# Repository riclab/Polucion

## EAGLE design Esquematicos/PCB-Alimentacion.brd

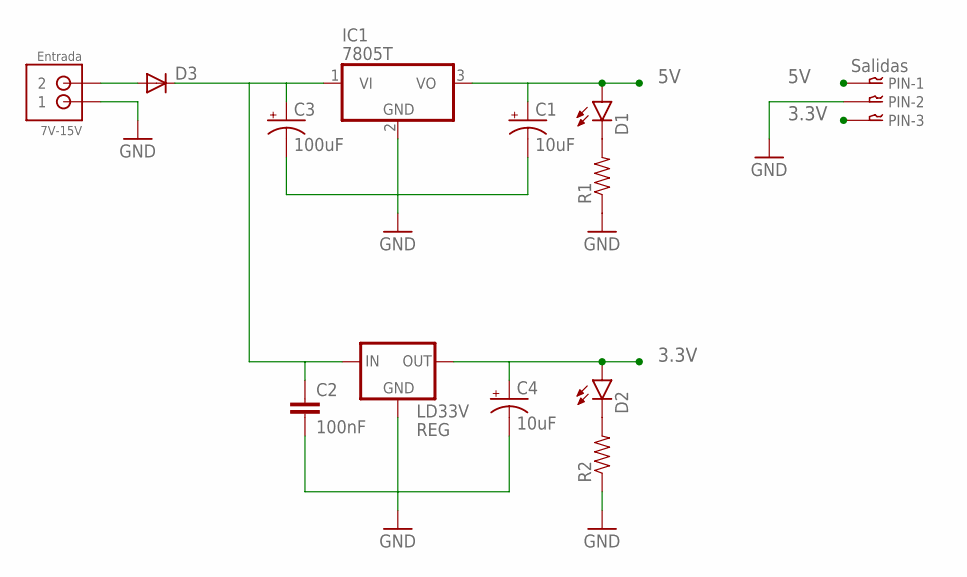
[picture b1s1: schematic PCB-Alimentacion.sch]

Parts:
7V-15V: Entrada; JST_B2B-PH_HEADER
C1, C4: 10uF; CPOL-RADIAL-10UF-25V
C2: 100nF; AXIAL-5MM
C3: 100uF; CPOL-RADIAL-10UF-25V
D1, D2: LED3MM
D3: DIODE-DO-214AC; DO-214AC
IC1: 7805T; TO220H
LD33V: REG; 78XXL
PIN: Salidas; B3B-XH
R1, R2: RESISTORKIT; AXIAL-0.3-KIT

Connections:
3.3V: C4.1 (+), D2.A, LD33V.GND (OUT), PIN.P$3
5V: C1.1 (+), D1.A, IC1.3 (VO), PIN.P$1
GND: 7V-15V.P1 (1), C1.2 (-), C2.P$2 (2), C3.2 (-), C4.2 (-), IC1.2 (GND), LD33V.IN (GND), PIN.P$2, R1.P$1 (1), R2.P$1 (1)
unnamed: C2.P$1 (1), C3.1 (+), D3.C, IC1.1 (VI), LD33V.OUT (IN)
unnamed: D1.K (C), R1.P$2 (2)
unnamed: 7V-15V.P2 (2), D3.A
unnamed: D2.K (C), R2.P$2 (2)

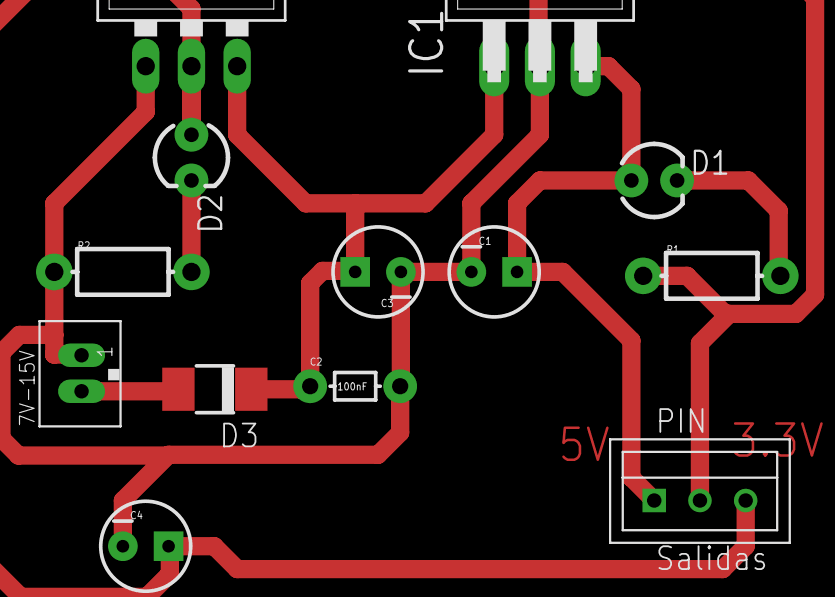
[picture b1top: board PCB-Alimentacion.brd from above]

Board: 2 copper layers, 13 parts (0 on the bottom side), 7 nets.

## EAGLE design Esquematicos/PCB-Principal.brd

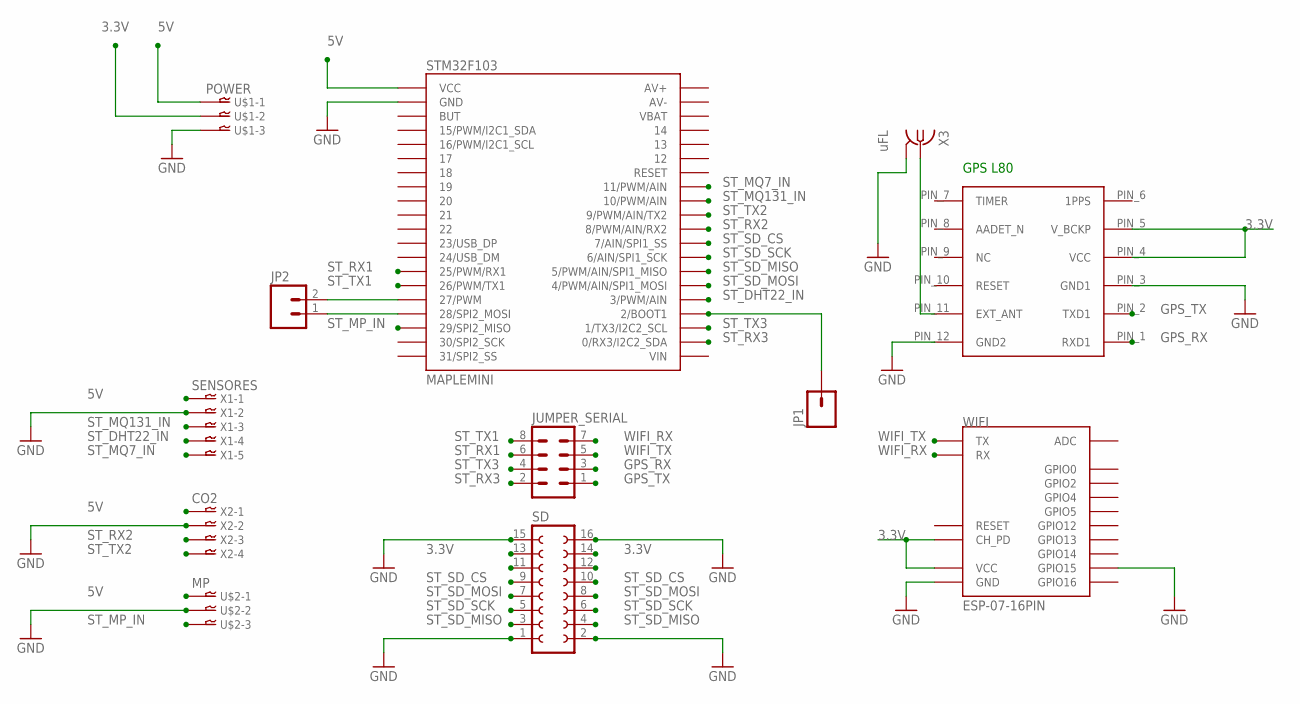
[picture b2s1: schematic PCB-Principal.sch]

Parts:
GPS1: GPSL80; L80
JP1: M01PTH_LONGPAD; 1X01_LONGPAD
JP2: M02PTH3; 1X02_LONGPADS
JUMPER_SERIAL: MA04-2
SD: FE08-2
STM32F103: MAPLEMINI; 20-DIP
U$1: POWER; B3B-XH
U$2: MP; B3B-XH
WIFI: ESP-07-16PIN
X1: SENSORES; B5B-XH
X2: CO2; B4B-XH
X3: uFL; IPEX-20279-001E

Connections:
3.3V: GPS1.PIN_4 (VCC), GPS1.PIN_5 (V_BCKP), SD.13, SD.14, U$1.P$2, WIFI.CH_PD, WIFI.VCC
5V: STM32F103.1 (VCC), U$1.P$1, U$2.P$1, X1.P$1, X2.P$1
GND: GPS1.PIN_3 (GND1), GPS1.PIN_12 (GND2), SD.1, SD.2, SD.15, SD.16, STM32F103.2 (GND), U$1.P$3, U$2.P$2, WIFI.GND, WIFI.GPIO15, X1.P$2, X2.P$2, X3.2@1 (GND), X3.2@2 (GND)
GPS_RX: GPS1.PIN_1 (RXD1), JUMPER_SERIAL.3
GPS_TX: GPS1.PIN_2 (TXD1), JUMPER_SERIAL.1
unnamed: JP1.1, STM32F103.24 (2/BOOT1)
unnamed: GPS1.PIN_11 (EXT_ANT), X3.1
unnamed: JP2.2, STM32F103.16 (27/PWM)
unnamed: JP2.1, STM32F103.17 (28/SPI2_MOSI)
ST_DHT22_IN: STM32F103.25 (3/PWM/AIN), X1.P$4
ST_MP_IN: STM32F103.18 (29/SPI2_MISO), U$2.P$3
ST_MQ7_IN: STM32F103.33 (11/PWM/AIN), X1.P$5
ST_MQ131_IN: STM32F103.32 (10/PWM/AIN), X1.P$3
ST_RX1: JUMPER_SERIAL.6, STM32F103.14 (25/PWM/RX1)
ST_RX2: STM32F103.30 (8/PWM/AIN/RX2), X2.P$3
ST_RX3: JUMPER_SERIAL.2, STM32F103.22 (0/RX3/I2C2_SDA)
ST_SD_CS: SD.9, SD.10, STM32F103.29 (7/AIN/SPI1_SS)
ST_SD_MISO: SD.3, SD.4, STM32F103.27 (5/PWM/AIN/SPI1_MISO)
ST_SD_MOSI: SD.7, SD.8, STM32F103.26 (4/PWM/AIN/SPI1_MOSI)
ST_SD_SCK: SD.5, SD.6, STM32F103.28 (6/AIN/SPI1_SCK)
ST_TX1: JUMPER_SERIAL.8, STM32F103.15 (26/PWM/TX1)
ST_TX2: STM32F103.31 (9/PWM/AIN/TX2), X2.P$4
ST_TX3: JUMPER_SERIAL.4, STM32F103.23 (1/TX3/I2C2_SCL)
WIFI_RX: JUMPER_SERIAL.7, WIFI.RX
WIFI_TX: JUMPER_SERIAL.5, WIFI.TX

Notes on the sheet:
GPS L80

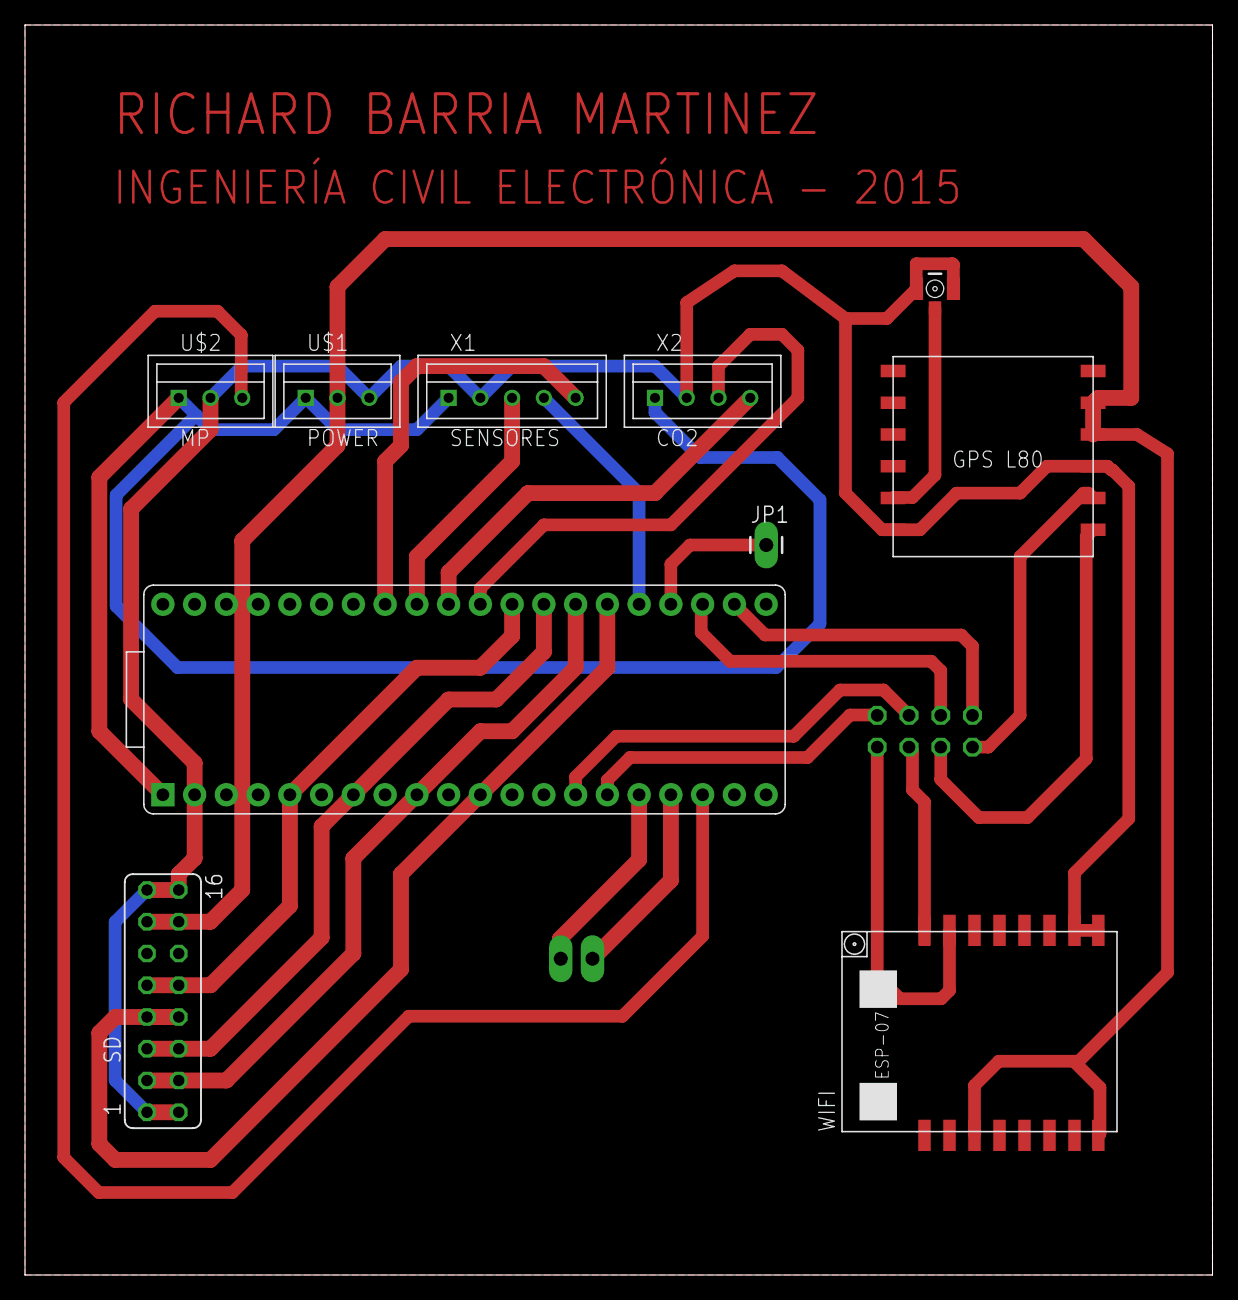
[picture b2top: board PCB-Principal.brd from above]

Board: 2 copper layers, 95.0 x 100.0 mm, 12 parts (1 on the bottom side), 25 nets.

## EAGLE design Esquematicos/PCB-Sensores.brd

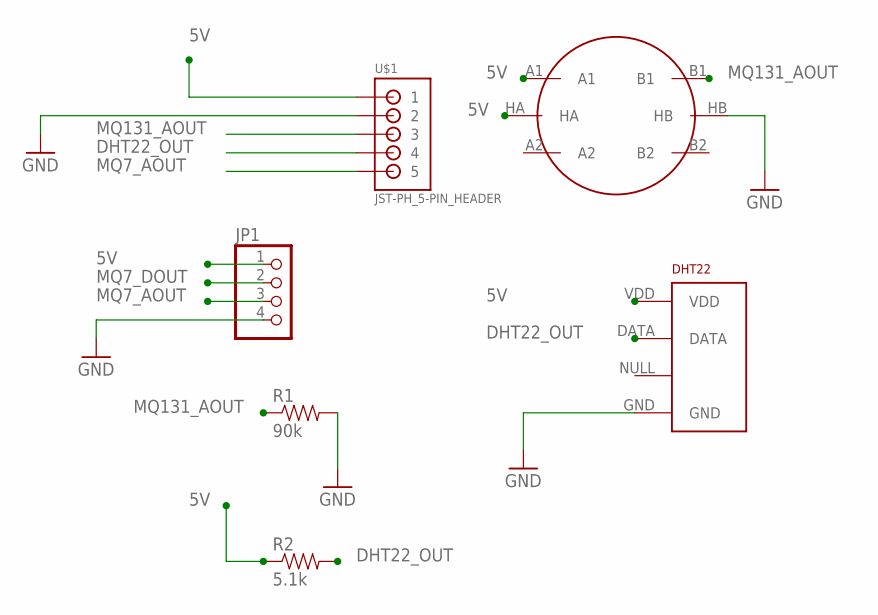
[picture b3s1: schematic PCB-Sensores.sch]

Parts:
DHT22: RHT03_DHT-22_AM2302; RHT03_DHT-22
JP1: PINHD-1X4; 1X04
MQ131: METHANE_SENSOR; MQ-3
R1: 90k; AXIAL-0.3EZ
R2: 5.1k; AXIAL-0.3EZ
U$1: JST-PH_5-PIN_HEADER; JST_B5B-PH_HEADER

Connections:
5V: DHT22.VDD, JP1.1, MQ131.A1, MQ131.HA, R2.P$1 (1), U$1.P1 (1)
DHT22_OUT: DHT22.DATA, R2.P$2 (2), U$1.P4 (4)
GND: DHT22.GND, JP1.4, MQ131.HB, R1.P$2 (2), U$1.P2 (2)
MQ7_AOUT: JP1.3, U$1.P5 (5)
MQ7_DOUT: JP1.2
MQ131_AOUT: MQ131.B1, R1.P$1 (1), U$1.P3 (3)

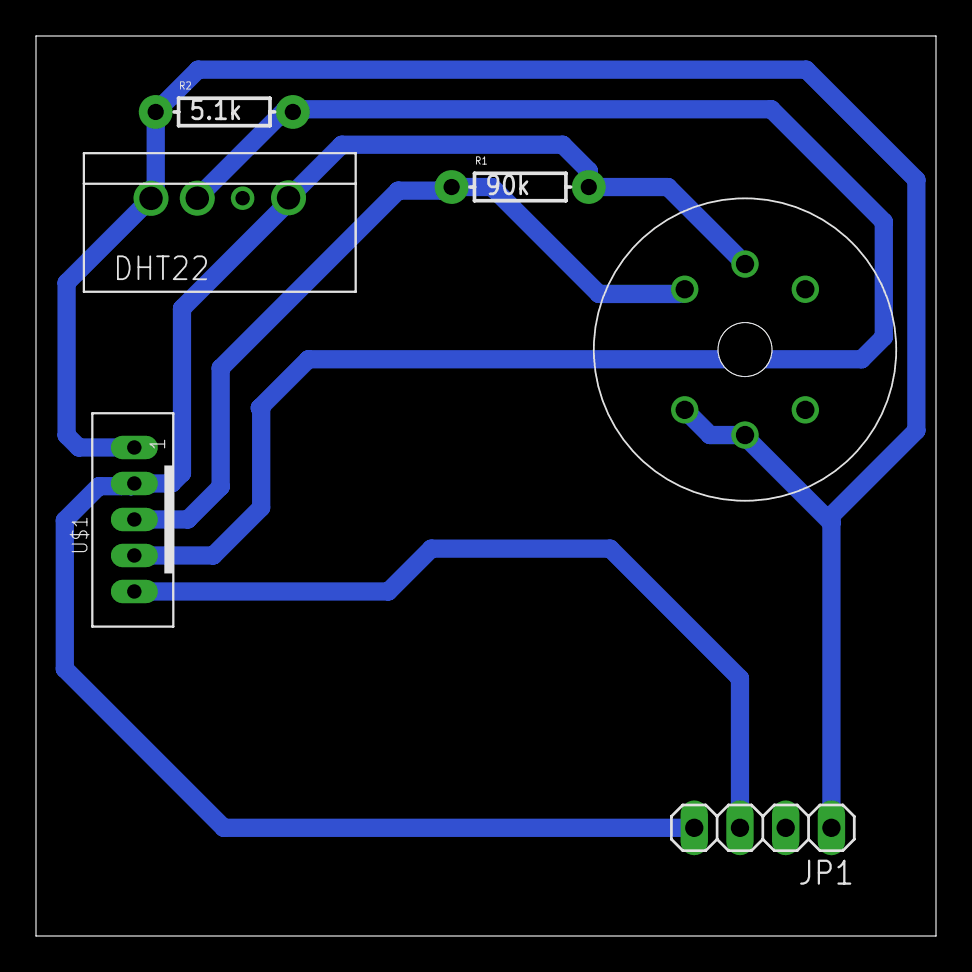
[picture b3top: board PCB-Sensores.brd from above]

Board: 2 copper layers, 50.0 x 50.0 mm, 6 parts (0 on the bottom side), 5 nets.

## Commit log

2016-11-01 inicial

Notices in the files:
parts and their libraries:
SparkFun-Passives: Licensing: Creative Commons ShareAlike 4.0 International - https://creativecommons.org/licenses/by-sa/4.0
